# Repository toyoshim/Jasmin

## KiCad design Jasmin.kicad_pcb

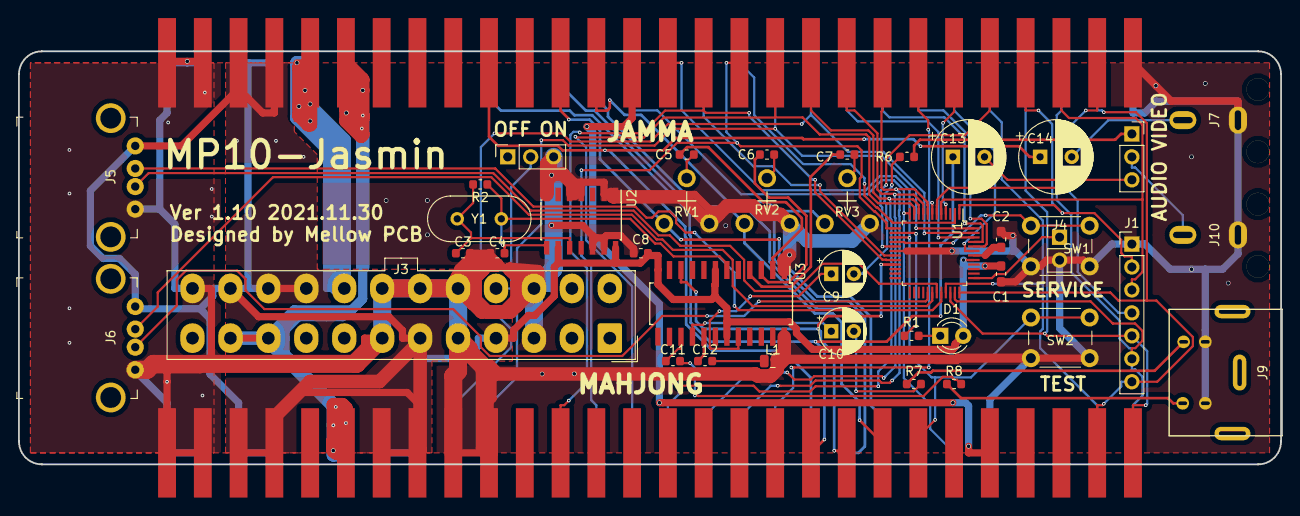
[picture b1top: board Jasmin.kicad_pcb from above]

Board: 2 copper layers, 139.7 x 45.7 mm, 42 parts (0 on the bottom side), 69 nets.

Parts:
C1: 100n; C_0603_1608Metric_Pad1.05x0.95mm_HandSolder
C2: 4.7u; C_0603_1608Metric_Pad1.05x0.95mm_HandSolder
C3, C4: 20p; C_0603_1608Metric
C5, C6, C7: 0.1u; C_0603_1608Metric
C8: C; C_0603_1608Metric
C9, C10: 220u; CP_Radial_D5.0mm_P2.50mm
C11: 0.47u; C_0603_1608Metric
C12: 27p; C_0603_1608Metric
C13, C14: 470u; CP_Radial_D8.0mm_P3.50mm
D1: LED; LED_D3.0mm
J1: KICK; PinHeader_1x07_P2.54mm_Vertical
J2: JAMMA; Connector_Edge_3.96mm_02x28_Row_JAMMA
J3: ATX-POWER; Molex_Mini-Fit_Jr_5566-24A_2x12_P4.20mm_Vertical
J4: UART; PinHeader_1x02_P2.54mm_Vertical
J5, J6: USB_A; USB_A_Female_UE27AC54100
J7: RCA-AUDIO; RCA-RJ-2410N
J8: MAHJONG; Connector_Edge_3.96mm_02x28_Row_JAMMA
J9: Mini-DIN-4-S; MINI-DIN-4-DI-6798-4
J10: RCA-VIDEO; RCA-RJ-2410N
L1: 68u; L_0805_2012Metric
R1: 1k; R_0603_1608Metric
R2: 1M; R_0603_1608Metric
R6, R7, R8: 75; R_0603_1608Metric
RV1, RV2, RV3: 2k; RV-RM-065
SW1, SW2: SW_Push; SW_PUSH_6mm_H4.3mm
SW3, SW4: SW_SPDT; PinSocket_1x03_P2.54mm_Vertical
U1: CH559; LQFP-48_7x7mm_P0.5mm
U2: 74HC86; SOIC-14_4.4x8.7mm_P1.27mm
U3: BH7236AF; SOIC-24_5.4x15.4mm_P1.27mm[BH7236]
Y1: 3.579545M; Crystal_HC49-4H_Vertical

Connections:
/1P1: J2.a22, J8.b11, U1.7
/1P2: J2.a23, U1.4
/1P3: J2.a24, U1.17
/1P4: J1.2, J2.a25, U1.1
/1P5: J1.3, J2.a26, U1.5
/1P6: J1.4, J2.a27, U1.6
/1PC: J2.a16, J8.a17, U1.20
/1PD: J2.a19, J8.b14, U1.10
/1PL: J2.a20, J8.b13, U1.9
/1PR: J2.a21, J8.b12, U1.8
/1PS: J2.a17, J8.b16, U1.13
/1PU: J2.a18, J8.b15, U1.11
/2P1: J2.b22, U1.44
/2P2: J2.b23, U1.43
/2P3: J2.b24, J8.b2, U1.33
/2P4: J1.5, J2.b25, J8.a1, U1.34
/2P5: J1.6, J2.b26, J8.b1, U1.35
/2P6: J1.7, J2.b27, J8.a2, U1.36
/2PC: J2.b16, U1.19
/2PD: J2.b19, J8.b20, U1.47
/2PL: J2.b20, U1.46
/2PR: J2.b21, U1.45
/2PS: J2.b17, U1.2
/2PU: J2.b18, J8.b19, U1.48
/3.3V: C2.1, U1.42
/12V: J2.a6, J2.b6, J3.10, J3.11, J8.a23, J8.b23
/-5V: J2.a5, J2.b5, J3.20
/B: J2.a13, J8.b9, RV3.1
/BOOT: SW1.1, U1.16
/Bin: C7.1, U3.4
/CSYNC: J2.b13, J8.a9, U1.21, U3.10
/G: J2.b12, J8.a8, RV2.1
/Gin: C6.1, U3.3
/H1_DM: J5.2, U1.32
/H1_DP: J5.3, U1.31
/H2_DM: J6.2, U1.30
/H2_DP: J6.3, U1.29
/LED: R1.2, U1.14
/PON: J3.16, SW3.2
/R: J2.a12, J8.b8, RV1.1
/Rin: C5.1, U3.2
/S+: C14.1, J2.a10, J8.b10
/S-: C13.1, J2.b10, J8.a10
/SCin: C4.1, R2.1, U2.8, U3.6, Y1.2
/SVC: J2.b14, J8.b6, U1.12
/S_C: J9.4, R8.1
/S_Y: J9.3, R7.1
/TEST: J2.a15, J8.a7, SW2.1, U1.15
/TXD: J4.1, U1.37
/VGND: J2.a14, J8.a5
/VIDEO: R6.1, SW4.1
/YTRAP: C12.2, U3.17
GND: C1.2, C2.2, C3.2, C4.2, C8.2, J1.1, J2.a1, J2.a2, J2.a28, J2.b1, J2.b2, J2.b28, J3.3, J3.5, J3.7, J3.15, J3.17, J3.18, J3.19, J3.24, J4.2, J5.4, J6.4, J7.2, J8.a19, J8.a20, J8.a27, J8.a28, J8.b5, J8.b27, J8.b28, J9.1, J9.2, J10.2, L1.1, RV1.3, RV2.3, RV3.3, SW1.2, SW2.2, SW3.3, U1.18, U2.1, U2.2, U2.4, U2.5, U2.7, U2.12, U2.13, U3.1, U3.24
unnamed: C3.1, R2.2, U2.10, Y1.1
unnamed: C5.2, RV1.2
unnamed: C6.2, RV2.2
unnamed: C7.2, RV3.2
unnamed: C9.1, U3.20
unnamed: C9.2, R6.2
unnamed: C10.1, U3.16
unnamed: C10.2, R7.2
unnamed: C11.1, R8.2
unnamed: C11.2, U3.15
unnamed: C12.1, L1.2
unnamed: C13.2, SW4.3
unnamed: C14.2, J7.1
unnamed: D1.1, R1.1
unnamed: J10.1, SW4.2
VCC: C1.1, C8.1, D1.2, J2.a3, J2.a4, J2.b3, J2.b4, J3.4, J3.6, J3.21, J3.22, J3.23, J5.1, J6.1, J8.a21, J8.a22, J8.a25, J8.a26, J8.b21, J8.b22, J8.b25, J8.b26, U1.41, U2.9, U2.14, U3.7, U3.12, U3.19

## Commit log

2021-11-23 import chlib
2021-11-23 Add LICENSE
2021-11-23 minimal firmware
2021-11-25 jamma support
2021-11-25 mahjong support
2022-08-22 experimental csync detection
2022-08-22 move into the firmware directory
2022-08-22 import PCB data
